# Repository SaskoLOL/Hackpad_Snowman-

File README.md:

# Hackpad_Snowman-
This is a self made 10 button pad with 4 leds!
There are 3 rows per 3 buttons, and then there is a top button! There is so much you can do with that button! I am not sure what it will do but I will do that later on!
# BOM:
Seeed XIAO RP2040 - 1x

SK6812 MINI-E LEDs - 4x

M3x16mm scre - 4x

3D PRINTED CASE ONLY. NO ACRYLIC.

MX-Style switches - 10x

# Screenshots of the Board:

 (I had 6 leds but I changed it to 4)

# Firmware:
I used KMK as a start for my Firmware

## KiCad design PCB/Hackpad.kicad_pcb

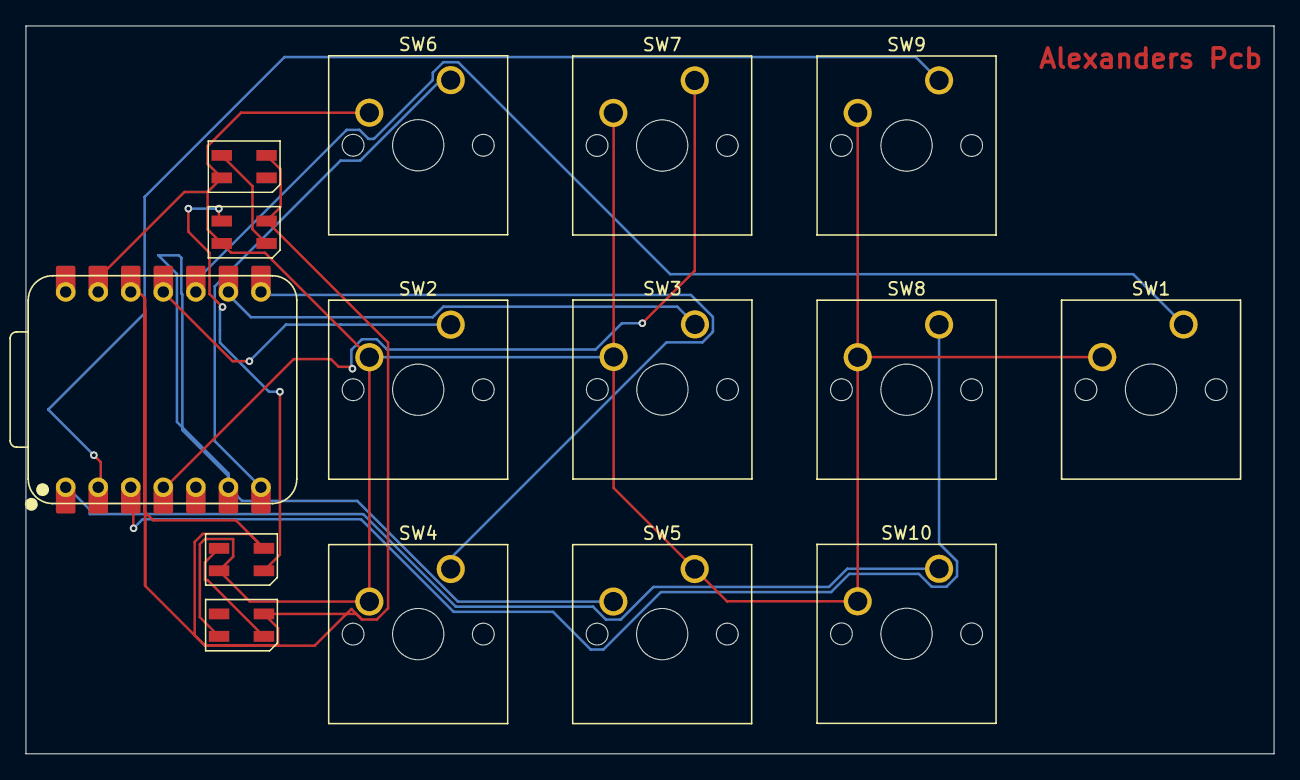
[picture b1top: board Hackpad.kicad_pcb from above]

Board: 2 copper layers, 97.4 x 56.8 mm, 15 parts (0 on the bottom side), 15 nets.

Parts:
D2, D3, D4, D5: SK6812MINI; LED_SK6812MINI_PLCC4_3.5x3.5mm_P1.75mm
SW1, SW2, SW3, SW4, SW5, SW6, SW7, SW8, SW9, SW10: SW_Push; SW_Cherry_MX_1.00u_PCB
U1: XIAO-RP2040-DIP

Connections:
+5V: D2.4 (VDD), D3.4 (VDD), D4.4 (VDD), D5.4 (VDD), U1.12 (3V3)
GND: D2.2 (VSS), D3.2 (VSS), D4.2 (VSS), D5.2 (VSS), SW1.2, SW2.2, SW3.2, SW4.2, SW5.1, SW6.2, SW7.2, SW8.2, SW9.2, SW10.2, U1.13 (GND)
unnamed: D2.1 (DOUT), D3.3 (DIN)
unnamed: D3.1 (DOUT), D4.3 (DIN)
unnamed: D4.1 (DOUT), D5.3 (DIN)
unnamed: SW6.1, U1.7 (GPIO0/TX)
unnamed: SW4.1, U1.8 (GPIO1/RX)
unnamed: SW3.1, U1.9 (GPIO2/SCK)
unnamed: SW2.1, U1.11 (GPIO3/MOSI)
unnamed: SW1.1, U1.10 (GPIO4/MISO)
unnamed: SW5.2, U1.6 (GPIO7/SCL)
unnamed: SW10.1, U1.1 (GPIO26/ADC0/A0)
unnamed: SW9.1, U1.2 (GPIO27/ADC1/A1)
unnamed: SW8.1, U1.3 (GPIO28/ADC2/A2)
unnamed: SW7.1, U1.4 (GPIO29/ADC3/A3)

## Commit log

2025-06-27 Create CAD
2025-06-27 Create test(ignore)
2025-06-27 Create text(ignore)
2025-06-27 Add files via upload
    Top of the case
2025-06-27 Add files via upload
    the bottom part
2025-06-28 Create test
